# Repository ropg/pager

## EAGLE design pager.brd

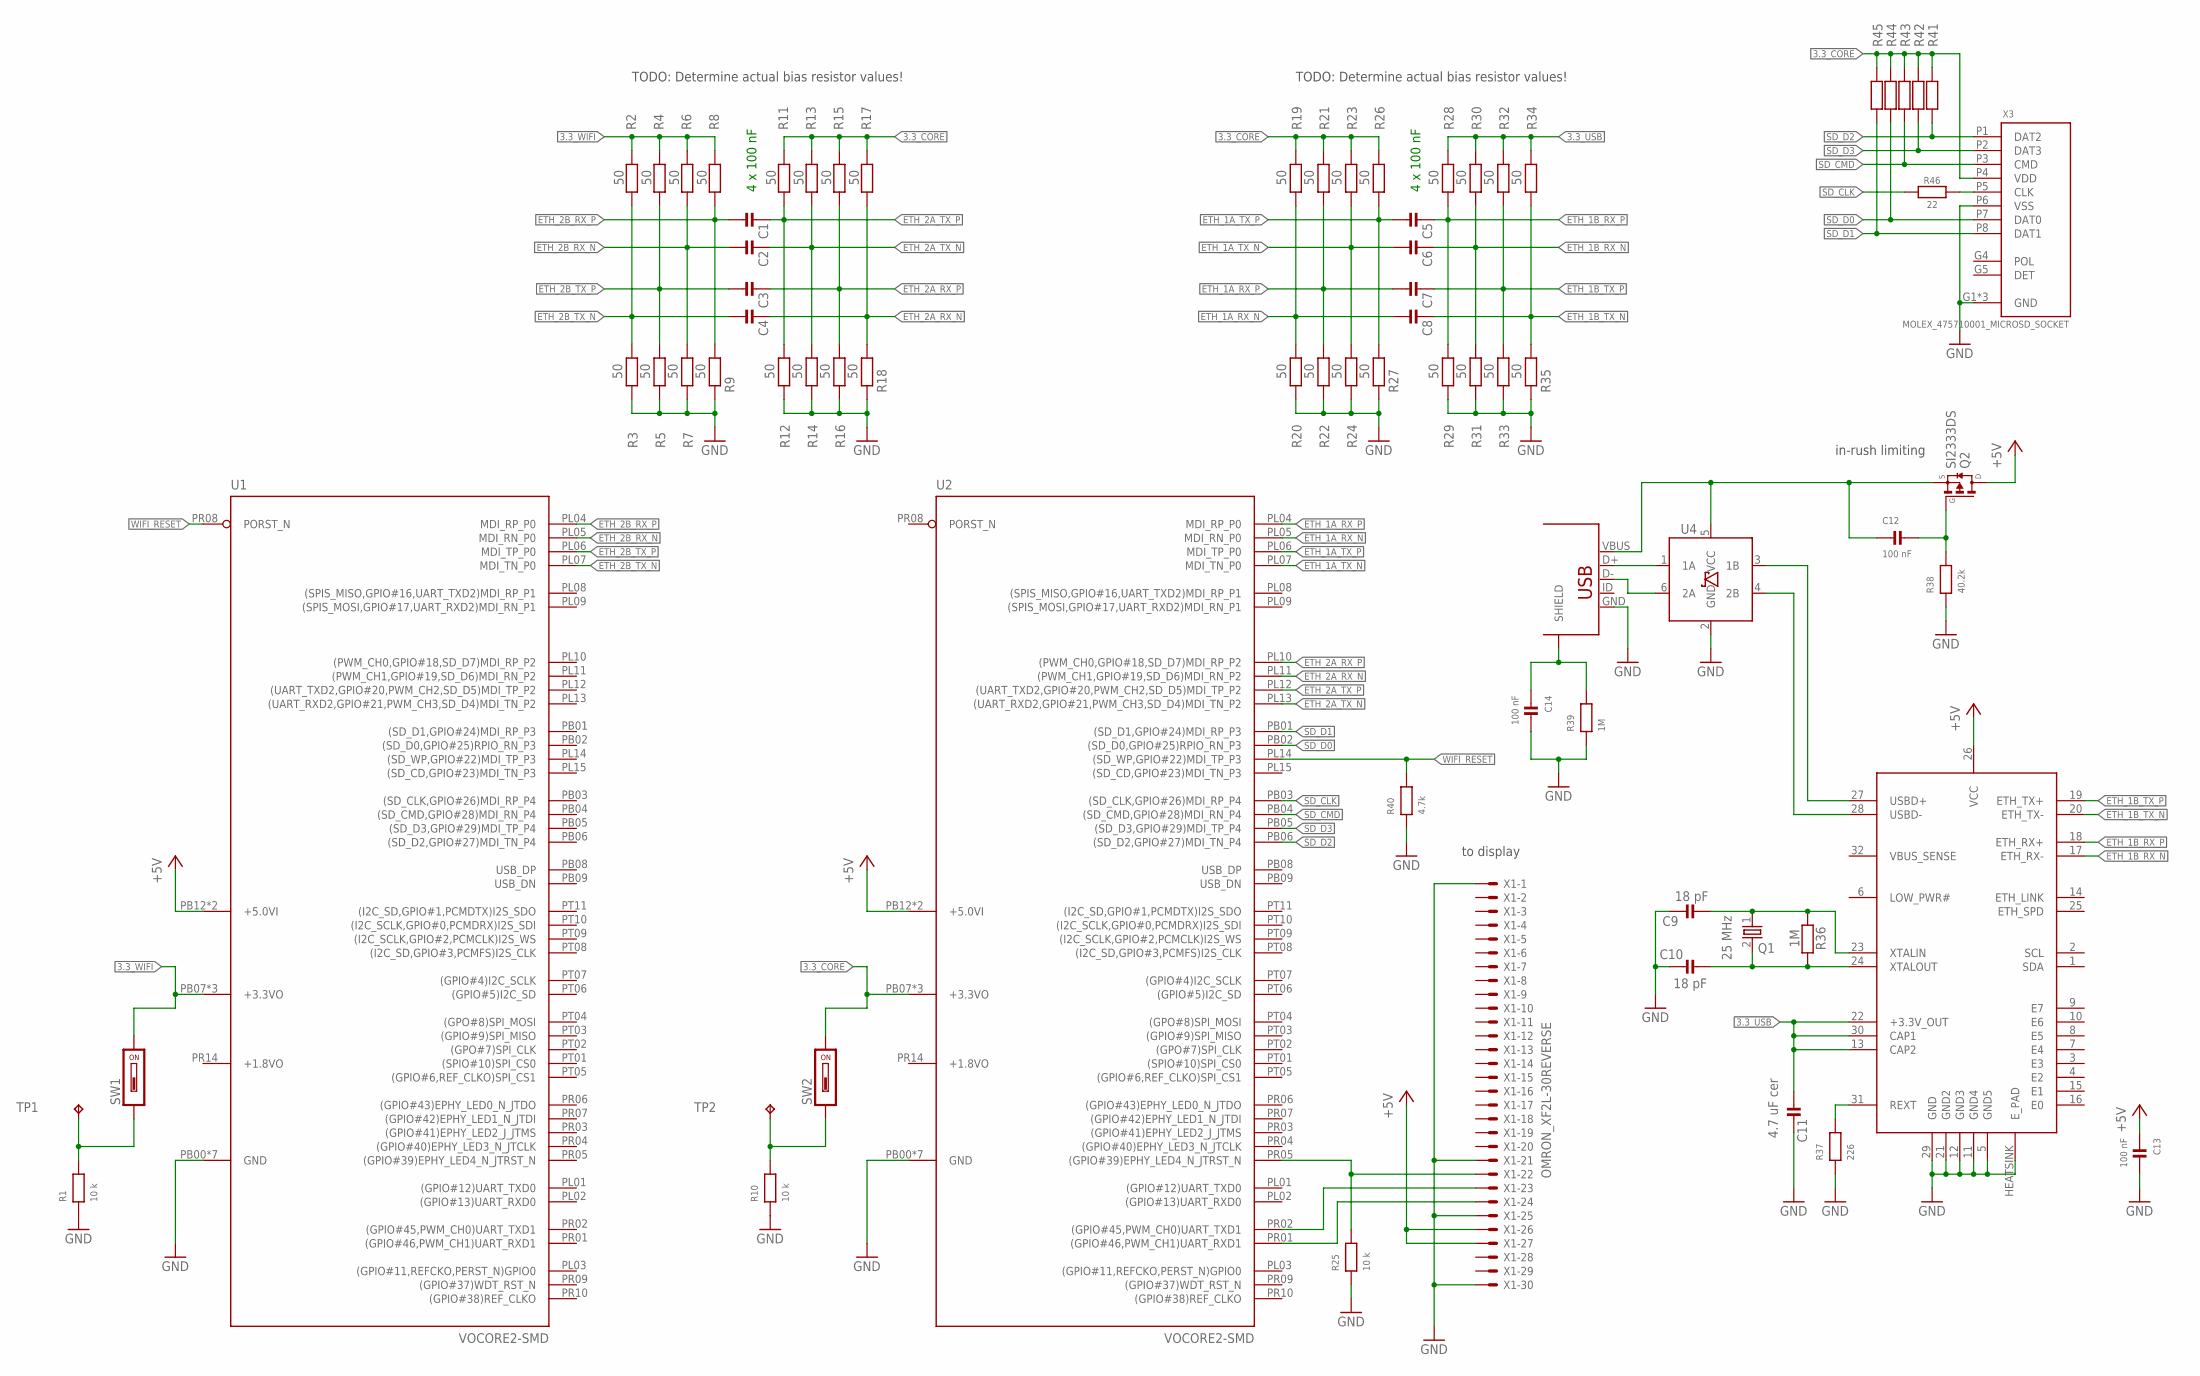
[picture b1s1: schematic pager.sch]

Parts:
C1, C2, C3, C4, C5, C6, C7, C8, C12, C13, C14: 100 nF; _0402
C9, C10: 18 pF; _0402
C11: 4.7 uF cer; _0603
Q1: 25 MHz; ABM3
Q2: SI2333DS; SOT23
R1, R10, R25: 10 k; _0402
R2, R3, R4, R5, R6, R7, R8, R9, R11, R12, R13, R14, R15, R16, R17, R18, R19, R20, R21, R22, R23, R24, R26, R27, R28, R29, R30, R31, R32, R33, R34, R35: 50; _0402
R36, R39: 1M; _0402
R37: 226; _0402
R38: 40.2k; _0402
R40: 4.7k; _0402
R41, R42, R43, R44, R45: 10k; _0402
R46: 22; _0402
SW1, SW2: CHS-01A1
TP1, TP2: TPTP16SQ; TP16SQ
U1, U2: VOCORE2-SMD
U3: XR22800IL; QFN32
U4: IP4234CZ6; TSOP-6
X1: OMRON_XF2L-30REVERSE; OMRON_XF2L-30
X2: FCI_8193_MICRO_USB; FCI_MICRO_USB_8193
X3: MOLEX_475710001_MICROSD_SOCKET

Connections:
3.3_CORE: R11.2, R13.2, R15.2, R17.2, R19.2, R21.2, R23.2, R26.2, R41.2, R42.2, R43.2, R44.2, R45.2, SW2.2, U2.PB07 (+3.3VO), U2.PL00 (+3.3VO), U2.PR11 (+3.3VO), X3.P4 (VDD)
3.3_USB: C11.1, R28.2, R30.2, R32.2, R34.2, U3.13 (CAP2), U3.22 (+3.3V_OUT), U3.30 (CAP1)
3.3_WIFI: R2.2, R4.2, R6.2, R8.2, SW1.2, U1.PB07 (+3.3VO), U1.PL00 (+3.3VO), U1.PR11 (+3.3VO)
+5V: C13.1, Q2.3 (D), U1.PB12 (+5.0VI), U1.PB13 (+5.0VI), U2.PB12 (+5.0VI), U2.PB13 (+5.0VI), U3.26 (VCC), X1.4, X1.5
DISP_RESET: R25.2, U2.PR05 ((GPIO#39)EPHY_LED4_N_JTRST_N), X1.9
DISP_RX0: U2.PR02 ((GPIO#45,PWM_CH0)UART_TXD1), X1.8
DISP_TX0: U2.PR01 ((GPIO#46,PWM_CH1)UART_RXD1), X1.7
ETH_1A_RX_N: C8.1, R19.1, R20.2, U2.PL05 (MDI_RN_P0)
ETH_1A_RX_P: C7.1, R21.1, R22.2, U2.PL04 (MDI_RP_P0)
ETH_1A_TX_N: C6.1, R23.1, R24.2, U2.PL07 (MDI_TN_P0)
ETH_1A_TX_P: C5.1, R26.1, R27.2, U2.PL06 (MDI_TP_P0)
ETH_1B_RX_N: C6.2, R30.1, R31.2, U3.17 (ETH_RX-)
ETH_1B_RX_P: C5.2, R28.1, R29.2, U3.18 (ETH_RX+)
ETH_1B_TX_N: C8.2, R34.1, R35.2, U3.20 (ETH_TX-)
ETH_1B_TX_P: C7.2, R32.1, R33.2, U3.19 (ETH_TX+)
ETH_2A_RX_N: C4.1, R17.1, R18.2, U2.PL11 ((PWM_CH1,GPIO#19,SD_D6)MDI_RN_P2)
ETH_2A_RX_P: C3.1, R15.1, R16.2, U2.PL10 ((PWM_CH0,GPIO#18,SD_D7)MDI_RP_P2)
ETH_2A_TX_N: C2.1, R13.1, R14.2, U2.PL13 ((UART_RXD2,GPIO#21,PWM_CH3,SD_D4)MDI_TN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)
ETH_2A_TX_P: C1.1, R11.1, R12.2, U2.PL12 ((UART_TXD2,GPIO#20,PWM_CH2,SD_D5)MDI_TP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)
ETH_2B_RX_N: C2.2, R6.1, R7.2, U1.PL05 (MDI_RN_P0)
ETH_2B_RX_P: C1.2, R8.1, R9.2, U1.PL04 (MDI_RP_P0)
ETH_2B_TX_N: C4.2, R2.1, R3.2, U1.PL07 (MDI_TN_P0)
ETH_2B_TX_P: C3.2, R4.1, R5.2, U1.PL06 (MDI_TP_P0)
GND: C9.1, C10.1, C11.2, C13.2, C14.2, R1.1, R3.1, R5.1, R7.1, R9.1, R10.1, R12.1, R14.1, R16.1, R18.1, R20.1, R22.1, R24.1, R25.1, R27.1, R29.1, R31.1, R33.1, R35.1, R37.1, R38.1, R39.1, R40.1, U1.PB00 (GND), U1.PB10 (GND), U1.PB11 (GND), U1.PR00 (GND), U1.PR12 (GND), U1.PR13 (GND), U1.PT00 (GND), U2.PB00 (GND), U2.PB10 (GND), U2.PB11 (GND), U2.PR00 (GND), U2.PR12 (GND), U2.PR13 (GND), U2.PT00 (GND), U3.5 (GND5), U3.11 (GND4), U3.12 (GND3), U3.21 (GND2), U3.29 (GND), U3.HEATSINK (E_PAD), U4.2 (GND), X1.1, X1.6, X1.10, X1.30, X2.GND, X3.G1 (GND), X3.G2 (GND), X3.G3 (GND), X3.P6 (VSS)
unnamed: R46.1, X3.P5 (CLK)
unnamed: R37.2, U3.31 (REXT)
unnamed: C10.2, Q1.2, R36.2, U3.24 (XTALOUT)
unnamed: C9.2, Q1.1, R36.1, U3.23 (XTALIN)
unnamed: C12.2, Q2.1 (G), R38.2
RAW_+5V: C12.1, Q2.2 (S), U4.5 (VCC), X2.VBUS
SD_CLK: R46.2, U2.PB03 ((SD_CLK,GPIO#26)MDI_RP_P4)
SD_CMD: R43.1, U2.PB04 ((SD_CMD,GPIO#28)MDI_RN_P4), X3.P3 (CMD)
SD_D0: R44.1, U2.PB02 ((SD_D0,GPIO#25)RPIO_RN_P3), X3.P7 (DAT0)
SD_D1: R45.1, U2.PB01 ((SD_D1,GPIO#24)MDI_RP_P3), X3.P8 (DAT1)
SD_D2: R41.1, U2.PB06 ((SD_D2,GPIO#27)MDI_TN_P4), X3.P1 (DAT2)
SD_D3: R42.1, U2.PB05 ((SD_D3,GPIO#29)MDI_TP_P4), X3.P2 (DAT3)
SHIELD: C14.1, R39.2, X2.MNT1 (SHIELD), X2.MNT2 (SHIELD), X2.MNT3 (SHIELD), X2.MNT4 (SHIELD), X2.P$1 (SHIELD), X2.P$2 (SHIELD)
USB_N: U3.28 (USBD-), U4.4 (2B)
USB_P: U3.27 (USBD+), U4.3 (1B)
USB_RAW_N: U4.6 (2A), X2.D-
USB_RAW_P: U4.1 (1A), X2.D+
WIFI_RESET: R40.2, U1.PR08 (PORST_N), U2.PL14 ((SD_WP,GPIO#22)MDI_TP_P3)
WP_CORE: R10.2, SW2.1, TP2.TP
WP_WIFI: R1.2, SW1.1, TP1.TP

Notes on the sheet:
in-rush limiting
to display
TODO: Determine actual bias resistor values!
4 x 100 nF

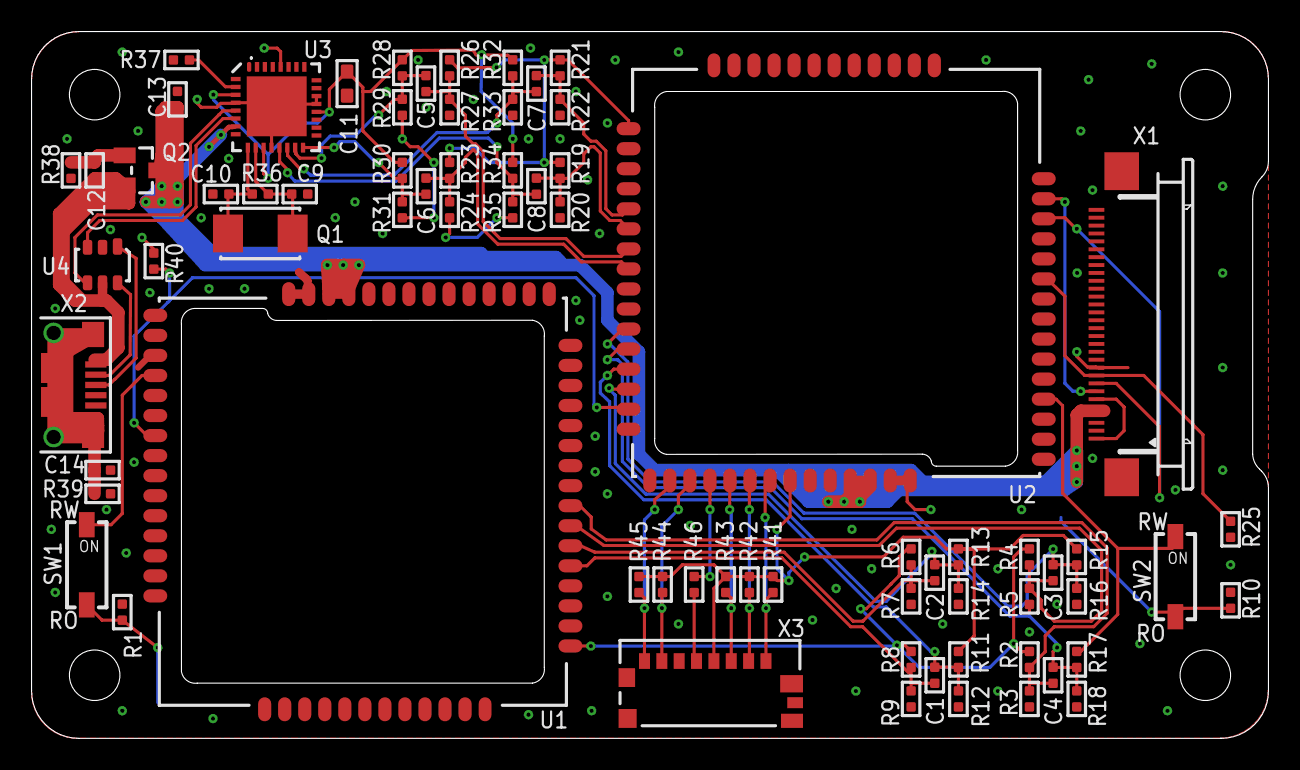
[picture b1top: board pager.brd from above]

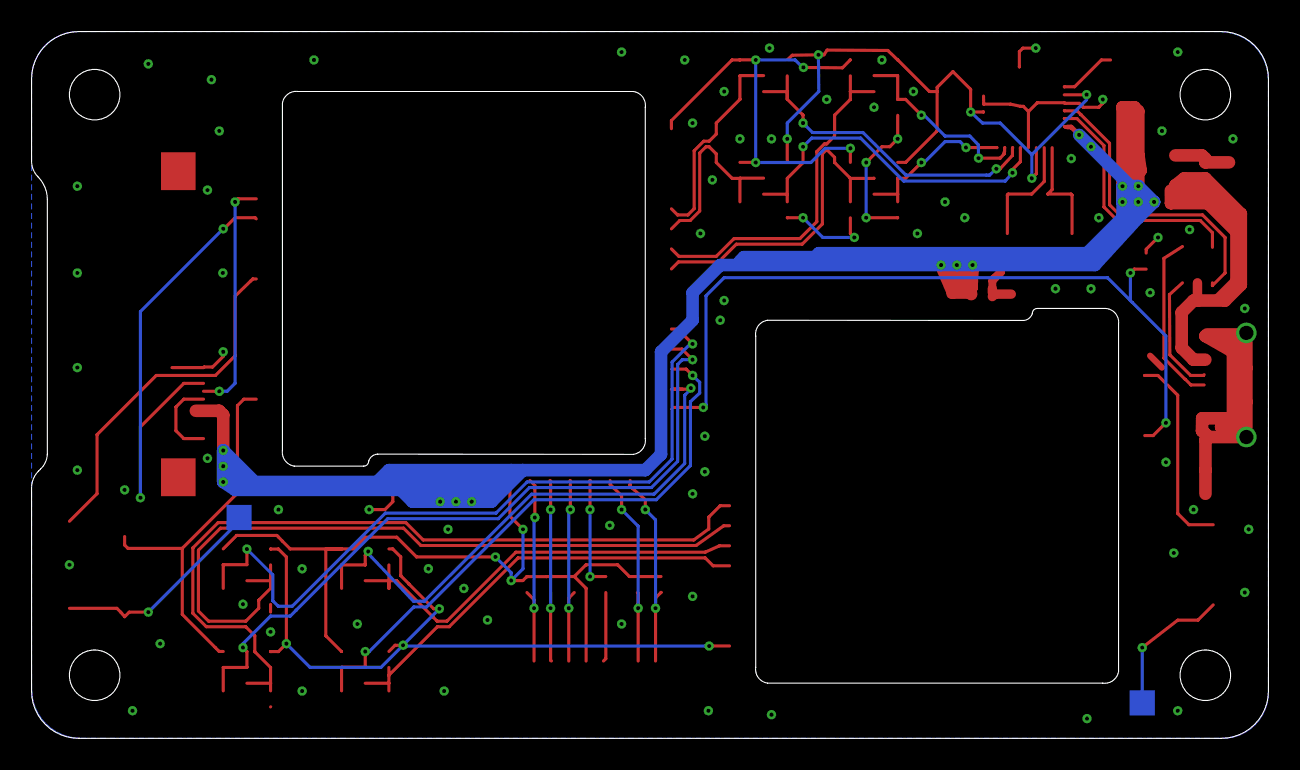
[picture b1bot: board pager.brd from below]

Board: 2 copper layers, 78.4 x 44.8 mm, 73 parts (2 on the bottom side), 44 nets.

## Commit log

2017-01-19 adding lib and gitignore
2017-01-19 Use 0402/0603 capacitors/resistors
2017-01-19 vocore: Add Name/Label to symbol + package
2017-01-19 Add UART test pads; shrink XTAL package
2017-01-19 add some missing junctions in schematics
2017-01-20 Add pull-down resistors for ethernet biasing networks
    Without knowing the internal schematics of the Ethernet PHY driver
    circuitry, we cannot assume that biasing to 3.3V is acceptable for all
    PHYs involved. For a number of PHYs, biasing must be done to 2.1V, for
    example. Hence, we need full resistive dividers to be able to set any
    bias voltage as needed. Actual resistor values TBD by experiments.
2017-01-20 move text notices to Info layer (they should't be in Nets layer)
2017-01-20 Use proper _N and _P suffix for ethernet and USB
    This is what the differential trace router of EAGLE requires for all
    differential traces, otherwise it will not consider the differential
    nature of the signals.
2017-01-20 Introduce Ethernet and USB Net Classes (and put signals in them)
    The trace geometry for differential impedance matching will differ for
    USB and Ethernet, so let's prepare this by putting them into their own
    net classes. Actual geometry still TBD in the net classes at some
    later point.
2017-01-20 placed origin in middle of vocore's, created board and dimensions, placed connectors
2017-01-28 placed parts, various small changes
    Removed test-pads for serial because different port has console and
    vocores come with nice big pads on top
2017-01-28 cosmetic fixes to schematic
2017-01-28 Slightly narrower pads on QFN32 to match design rules
2017-01-28 trying to route
    Will be ripped up, just to see
2017-02-03 Fixed some parts, better placement
2017-02-03 moved R25 for better prototype soldering access
2017-02-04 Added wifi_reset wire, polygons on tRestrict for Vocore's and routed power bus and USB
2017-02-04 Routed
2017-02-04 5V to USB chip nicer
2017-02-05 moved wire to make ground-plane continue better between U1 and U2
2017-02-06 Newer board file, laforge's tips mostly incorporated
2017-02-06 Some via's were double
2017-02-06 ground plane segments better connected
2017-02-06 fixed a wire too close to pads
2017-02-06 Ground planes even nicer
2017-02-07 Added TVS, resistor and cap between USB-shield and GND, made +5V bus 0.8 mm thick
2017-02-07 minor fixes
2017-02-07 two more GND vias
2017-02-07 various small fixes
2017-02-07 moves to make more space around mounting holes
2017-02-07 Moved vias away from under metallic components
2017-02-07 fix to a trace
2017-02-07 turned off bottom silk screen, minor move of a trace
2017-02-09 moved R25 and fixed a wire that had become an air wire again during a move.
2017-02-10 Fix wire that had come loose.
2017-02-10 vias to 0.25mm drill, 0.6mm diameter
2017-02-12 placed R40 to pull down wifi-reset
    Not sure whether good idea, it's a trade-off. We can always not
    populate.
2017-02-12 added two more vias at +5V feed, moved two vias to make ground plane continuous
2017-02-12 fix drc error
2017-02-12 even thicker power bus
2017-02-12 a few extra ground-plane vias
2017-02-13 added SD-card
2017-02-13 minor silkscreen fixes
2017-02-13 stop margin 0mil
